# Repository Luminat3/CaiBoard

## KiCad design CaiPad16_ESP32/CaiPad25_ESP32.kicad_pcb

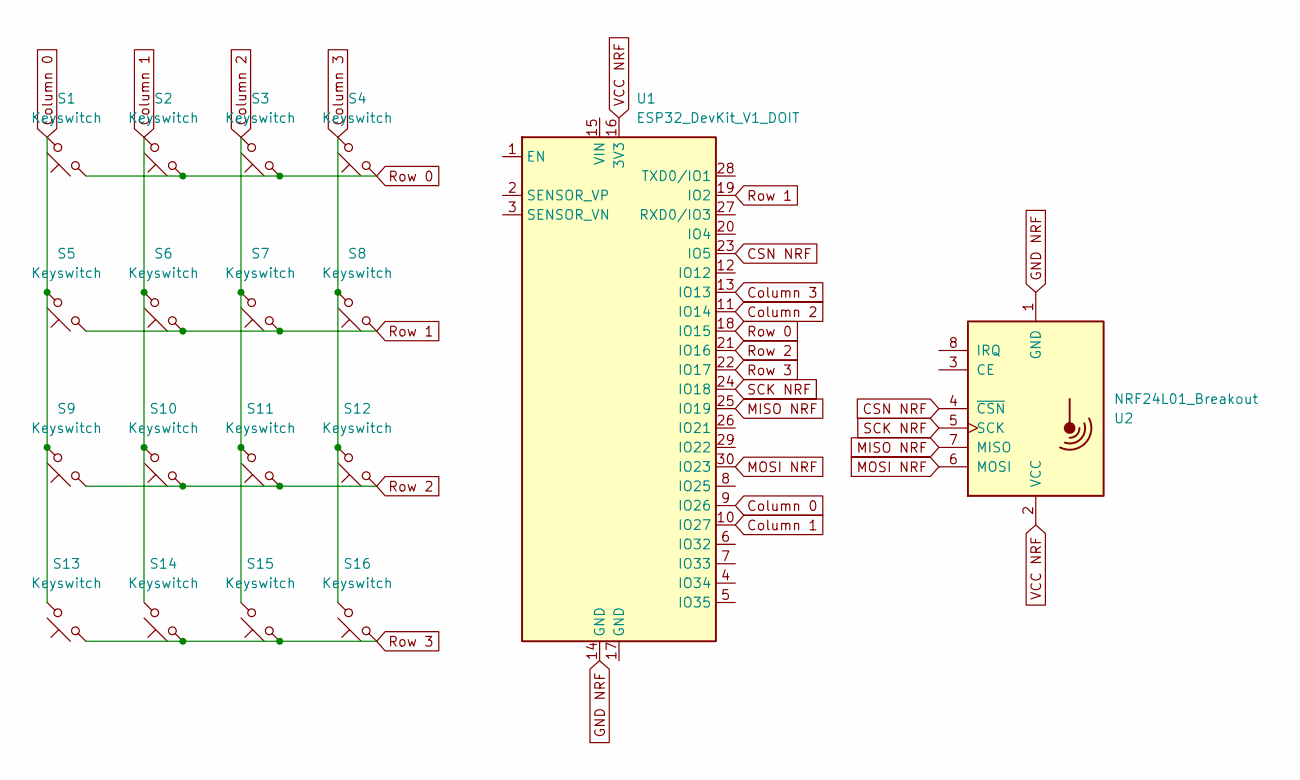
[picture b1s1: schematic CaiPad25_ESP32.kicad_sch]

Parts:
S1, S2, S3, S4, S5, S6, S7, S8, S9, S10, S11, S12, S13, S14, S15, S16: Keyswitch; SW_Cherry_MX_1.00u_PCB
U1: ESP32_DevKit_V1_DOIT; esp32_devkit_v1_doit
U2: NRF24L01_Breakout; nRF24L01_Breakout

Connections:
CSN NRF: U1.23 (IO5), U2.4 (~CSN)
Column 0: S1.2, S5.2, S9.2, S13.2, U1.9 (IO26)
Column 1: S2.2, S6.2, S10.2, S14.2, U1.10 (IO27)
Column 2: S3.2, S7.2, S11.2, S15.2, U1.11 (IO14)
Column 3: S4.2, S8.2, S12.2, S16.2, U1.13 (IO13)
GND NRF: U1.14 (GND), U2.1 (GND)
MISO NRF: U1.25 (IO19), U2.7 (MISO)
MOSI NRF: U1.30 (IO23), U2.6 (MOSI)
Row 0: S1.1, S2.1, S3.1, S4.1, U1.18 (IO15)
Row 1: S5.1, S6.1, S7.1, S8.1, U1.19 (IO2)
Row 2: S9.1, S10.1, S11.1, S12.1, U1.21 (IO16)
Row 3: S13.1, S14.1, S15.1, S16.1, U1.22 (IO17)
SCK NRF: U1.24 (IO18), U2.5 (SCK)
VCC NRF: U1.16 (3V3), U2.2 (VCC)

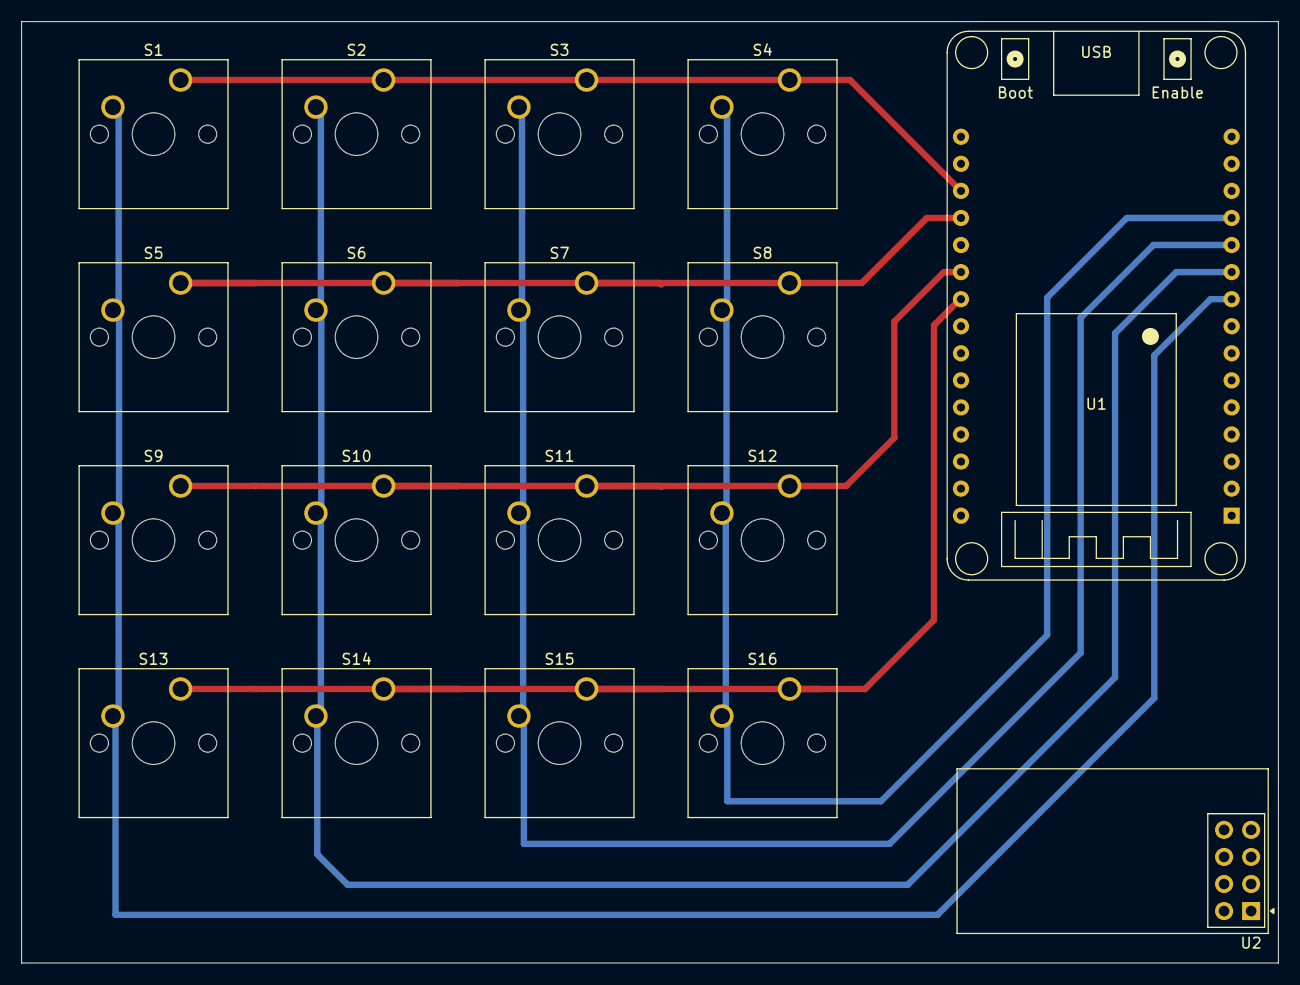
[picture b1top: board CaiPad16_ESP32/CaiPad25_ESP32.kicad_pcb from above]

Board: 2 copper layers, 117.9 x 88.3 mm, 18 parts (0 on the bottom side), 14 nets.

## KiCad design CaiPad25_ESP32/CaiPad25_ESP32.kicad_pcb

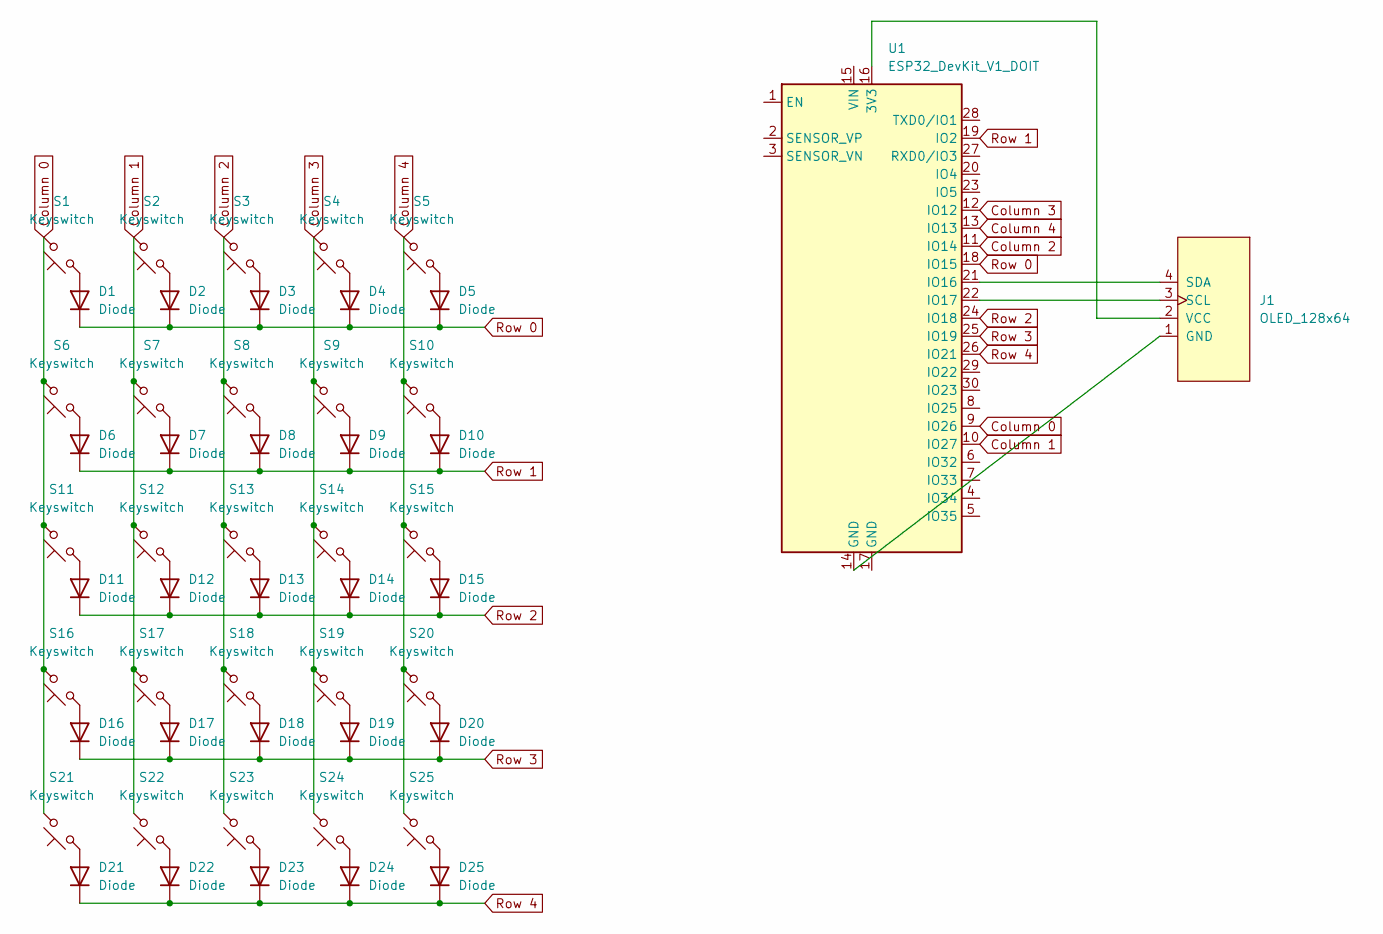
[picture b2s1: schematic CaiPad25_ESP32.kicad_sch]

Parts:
D1, D2, D3, D4, D5, D6, D7, D8, D9, D10, D11, D12, D13, D14, D15, D16, D17, D18, D19, D20, D21, D22, D23, D24, D25: Diode; Diode_DO-35
J1: OLED_128x64
S1, S2, S3, S4, S5, S6, S7, S8, S9, S10, S11, S12, S13, S14, S15, S16, S17, S18, S19, S20, S21, S22, S23, S24, S25: Keyswitch; SW_Cherry_MX_1.00u_PCB
U1: ESP32_DevKit_V1_DOIT; esp32_devkit_v1_doit

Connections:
Column 0: S1.2, S6.2, S11.2, S16.2, S21.2, U1.9 (IO26)
Column 1: S2.2, S7.2, S12.2, S17.2, S22.2, U1.10 (IO27)
Column 2: S3.2, S8.2, S13.2, S18.2, S23.2, U1.11 (IO14)
Column 3: S4.2, S9.2, S14.2, S19.2, S24.2, U1.12 (IO12)
Column 4: S5.2, S10.2, S15.2, S20.2, S25.2, U1.13 (IO13)
unnamed: D1.2 (A), S1.1
unnamed: D2.2 (A), S2.1
unnamed: D3.2 (A), S3.1
unnamed: D4.2 (A), S4.1
unnamed: D5.2 (A), S5.1
unnamed: D6.2 (A), S6.1
unnamed: D7.2 (A), S7.1
unnamed: D8.2 (A), S8.1
unnamed: D9.2 (A), S9.1
unnamed: D10.2 (A), S10.1
unnamed: D11.2 (A), S11.1
unnamed: D12.2 (A), S12.1
unnamed: D13.2 (A), S13.1
unnamed: D14.2 (A), S14.1
unnamed: D15.2 (A), S15.1
unnamed: D16.2 (A), S16.1
unnamed: D17.2 (A), S17.1
unnamed: D18.2 (A), S18.1
unnamed: D19.2 (A), S19.1
unnamed: D20.2 (A), S20.1
unnamed: D21.2 (A), S21.1
unnamed: D22.2 (A), S22.1
unnamed: D23.2 (A), S23.1
unnamed: D24.2 (A), S24.1
unnamed: D25.2 (A), S25.1
unnamed: J1.1 (GND), U1.14 (GND)
unnamed: J1.3 (SCL), U1.22 (IO17)
unnamed: J1.4 (SDA), U1.21 (IO16)
unnamed: J1.2 (VCC), U1.16 (3V3)
Row 0: D1.1 (K), D2.1 (K), D3.1 (K), D4.1 (K), D5.1 (K), U1.18 (IO15)
Row 1: D6.1 (K), D7.1 (K), D8.1 (K), D9.1 (K), D10.1 (K), U1.19 (IO2)
Row 2: D11.1 (K), D12.1 (K), D13.1 (K), D14.1 (K), D15.1 (K), U1.24 (IO18)
Row 3: D16.1 (K), D17.1 (K), D18.1 (K), D19.1 (K), D20.1 (K), U1.25 (IO19)
Row 4: D21.1 (K), D22.1 (K), D23.1 (K), D24.1 (K), D25.1 (K), U1.26 (IO21)

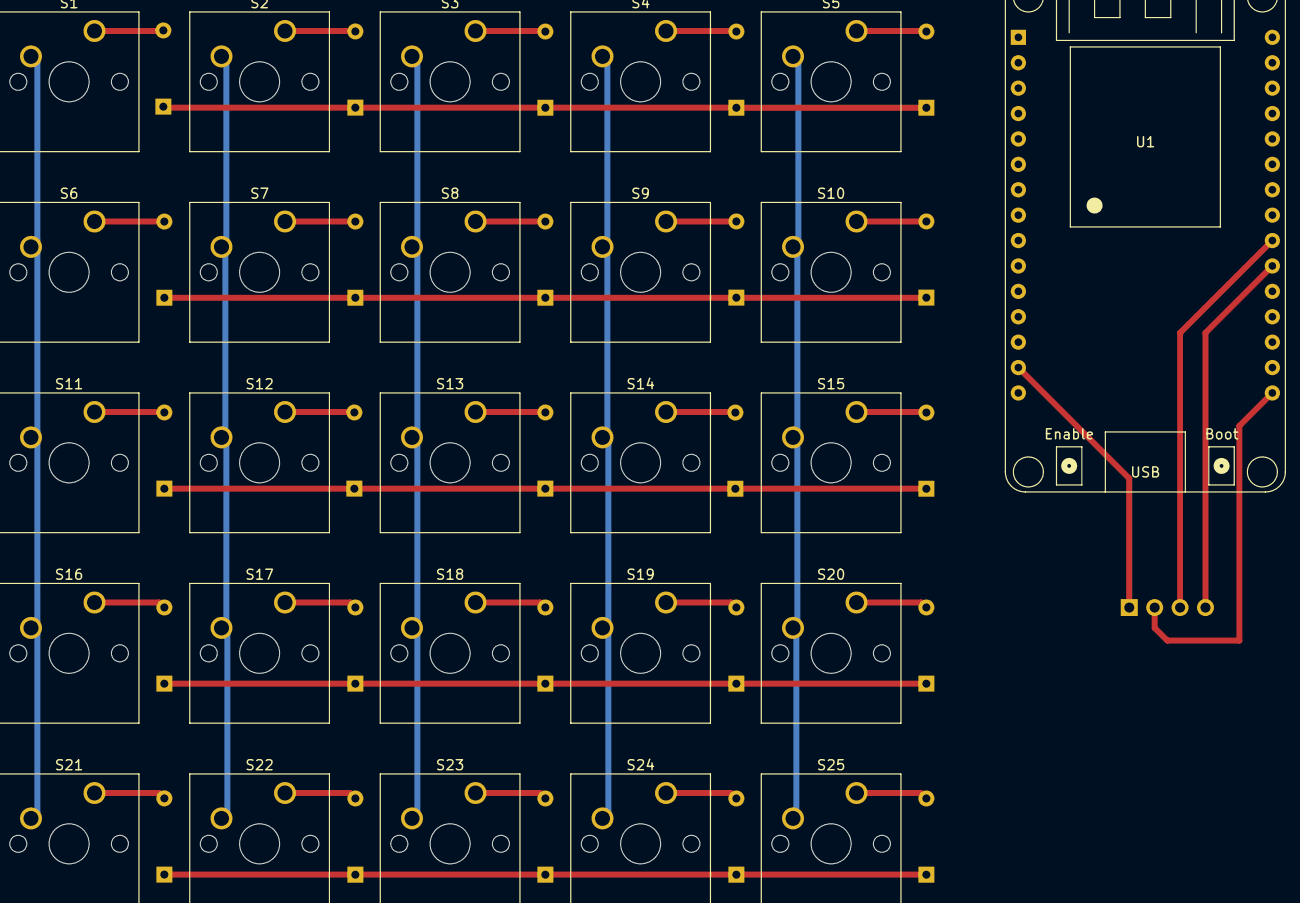
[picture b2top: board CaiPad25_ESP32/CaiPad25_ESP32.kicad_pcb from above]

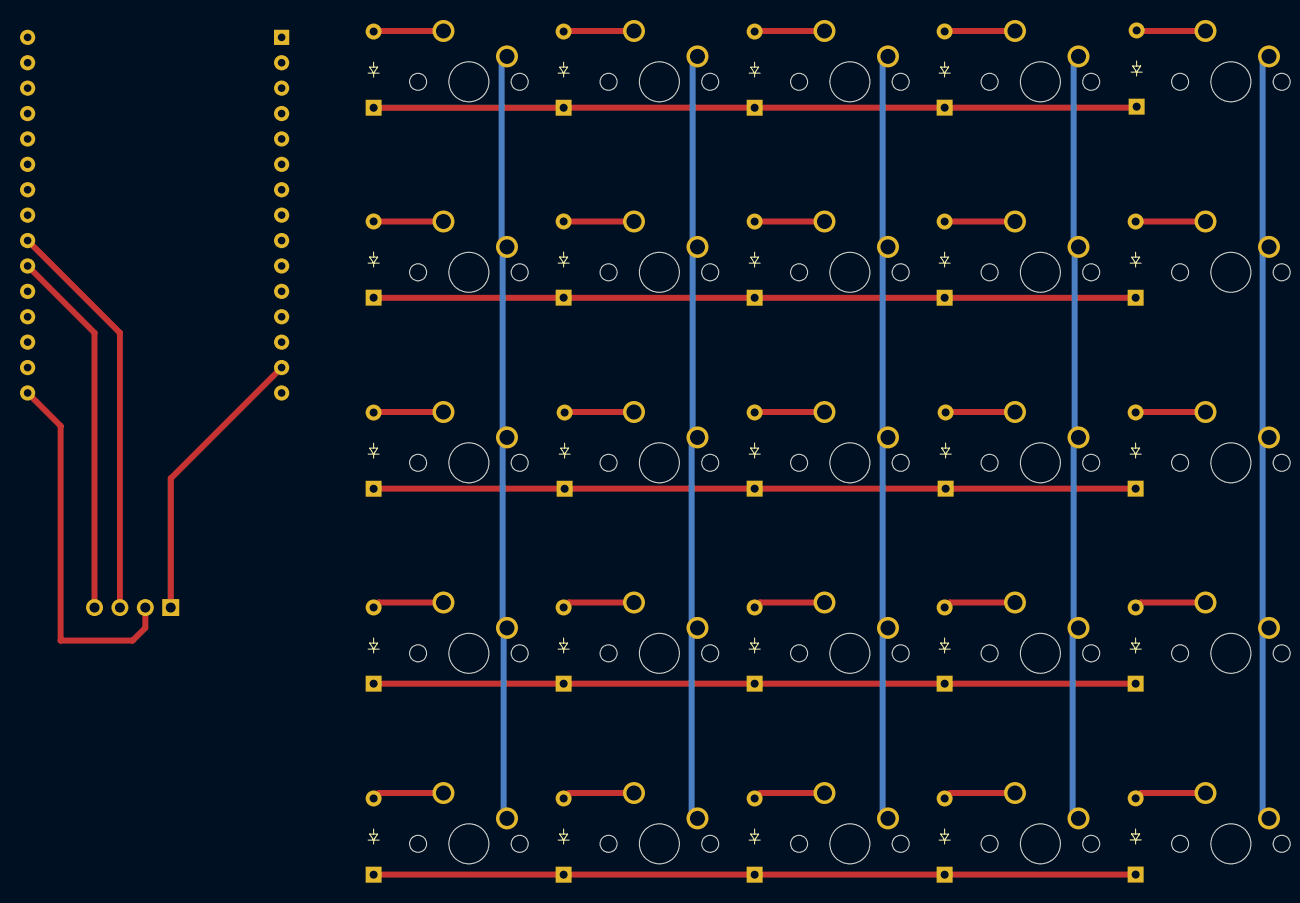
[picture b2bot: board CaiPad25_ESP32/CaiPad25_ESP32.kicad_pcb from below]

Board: 2 copper layers, 52 parts (25 on the bottom side), 39 nets.

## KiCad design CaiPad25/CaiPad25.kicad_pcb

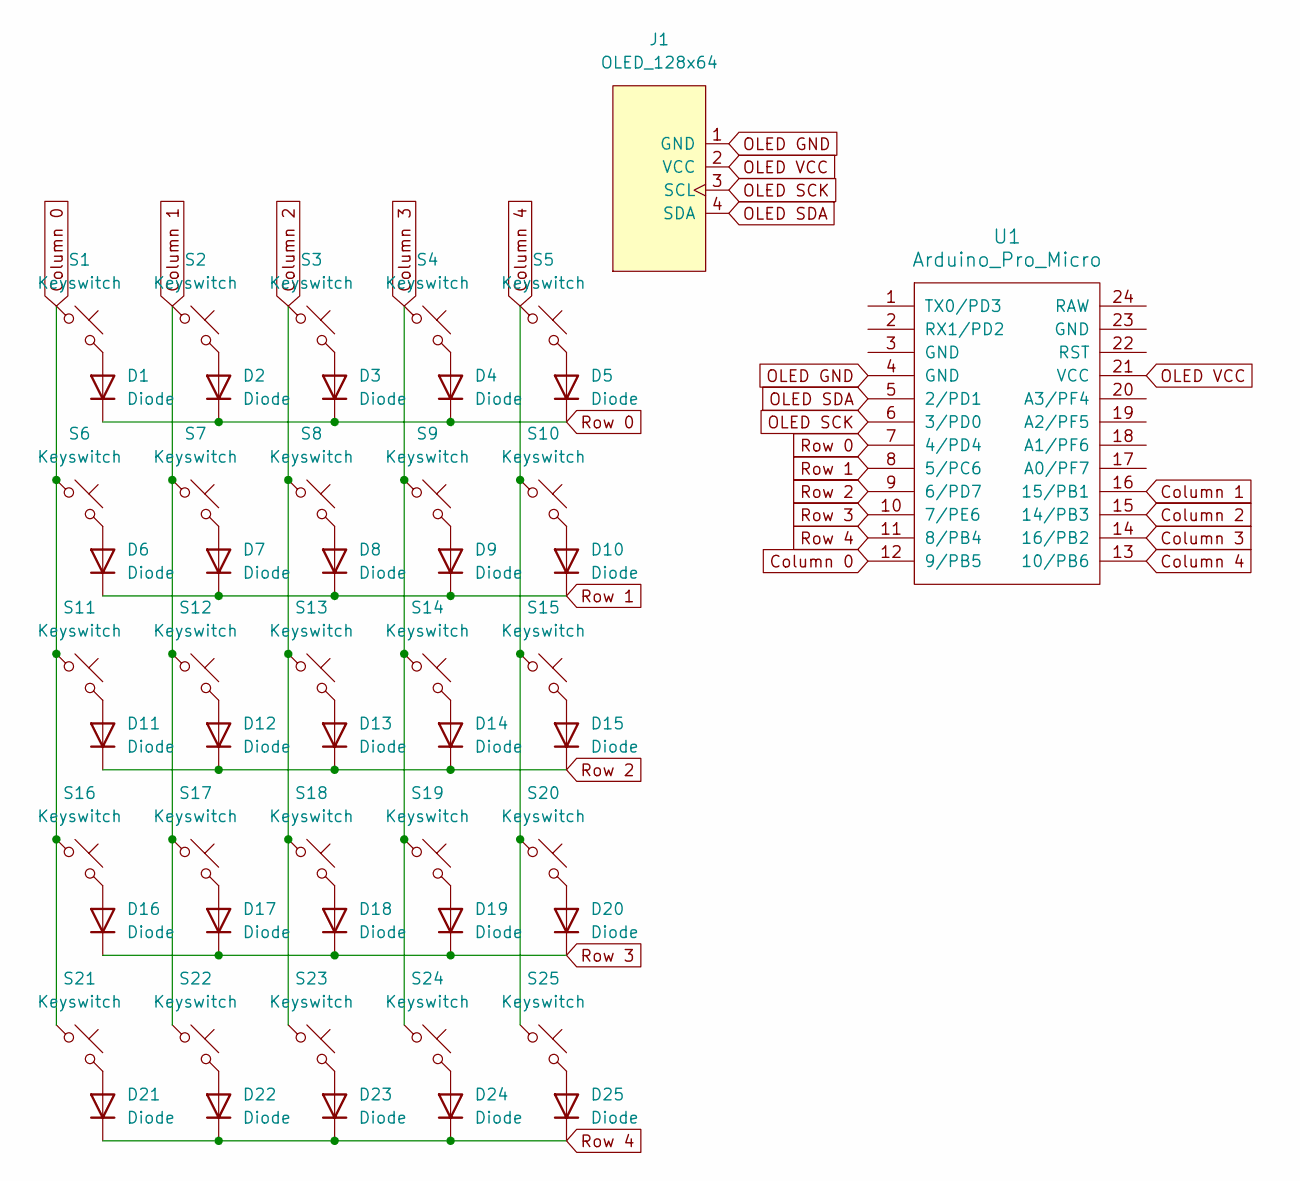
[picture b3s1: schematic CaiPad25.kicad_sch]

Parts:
D1, D2, D3, D4, D5, D6, D7, D8, D9, D10, D11, D12, D13, D14, D15, D16, D17, D18, D19, D20, D21, D22, D23, D24, D25: Diode; Diode_DO-35
J1: OLED_128x64
S1, S2, S3, S4, S5, S6, S7, S8, S9, S10, S11, S12, S13, S14, S15, S16, S17, S18, S19, S20, S21, S22, S23, S24, S25: Keyswitch; MX_PCB_1.00u
U1: Arduino_Pro_Micro

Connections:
Column 0: S1.1, S6.1, S11.1, S16.1, S21.1, U1.12 (9/PB5)
Column 1: S2.1, S7.1, S12.1, S17.1, S22.1, U1.16 (15/PB1)
Column 2: S3.1, S8.1, S13.1, S18.1, S23.1, U1.15 (14/PB3)
Column 3: S4.1, S9.1, S14.1, S19.1, S24.1, U1.14 (16/PB2)
Column 4: S5.1, S10.1, S15.1, S20.1, S25.1, U1.13 (10/PB6)
unnamed: D1.2 (A), S1.2
unnamed: D2.2 (A), S2.2
unnamed: D3.2 (A), S3.2
unnamed: D4.2 (A), S4.2
unnamed: D5.2 (A), S5.2
unnamed: D6.2 (A), S6.2
unnamed: D7.2 (A), S7.2
unnamed: D8.2 (A), S8.2
unnamed: D9.2 (A), S9.2
unnamed: D10.2 (A), S10.2
unnamed: D11.2 (A), S11.2
unnamed: D12.2 (A), S12.2
unnamed: D13.2 (A), S13.2
unnamed: D14.2 (A), S14.2
unnamed: D15.2 (A), S15.2
unnamed: D16.2 (A), S16.2
unnamed: D17.2 (A), S17.2
unnamed: D18.2 (A), S18.2
unnamed: D19.2 (A), S19.2
unnamed: D20.2 (A), S20.2
unnamed: D21.2 (A), S21.2
unnamed: D22.2 (A), S22.2
unnamed: D23.2 (A), S23.2
unnamed: D24.2 (A), S24.2
unnamed: D25.2 (A), S25.2
OLED GND: J1.1 (GND), U1.4 (GND)
OLED SCK: J1.3 (SCL), U1.6 (3/PD0)
OLED SDA: J1.4 (SDA), U1.5 (2/PD1)
OLED VCC: J1.2 (VCC), U1.21 (VCC)
Row 0: D1.1 (K), D2.1 (K), D3.1 (K), D4.1 (K), D5.1 (K), U1.7 (4/PD4)
Row 1: D6.1 (K), D7.1 (K), D8.1 (K), D9.1 (K), D10.1 (K), U1.8 (5/PC6)
Row 2: D11.1 (K), D12.1 (K), D13.1 (K), D14.1 (K), D15.1 (K), U1.9 (6/PD7)
Row 3: D16.1 (K), D17.1 (K), D18.1 (K), D19.1 (K), D20.1 (K), U1.10 (7/PE6)
Row 4: D21.1 (K), D22.1 (K), D23.1 (K), D24.1 (K), D25.1 (K), U1.11 (8/PB4)

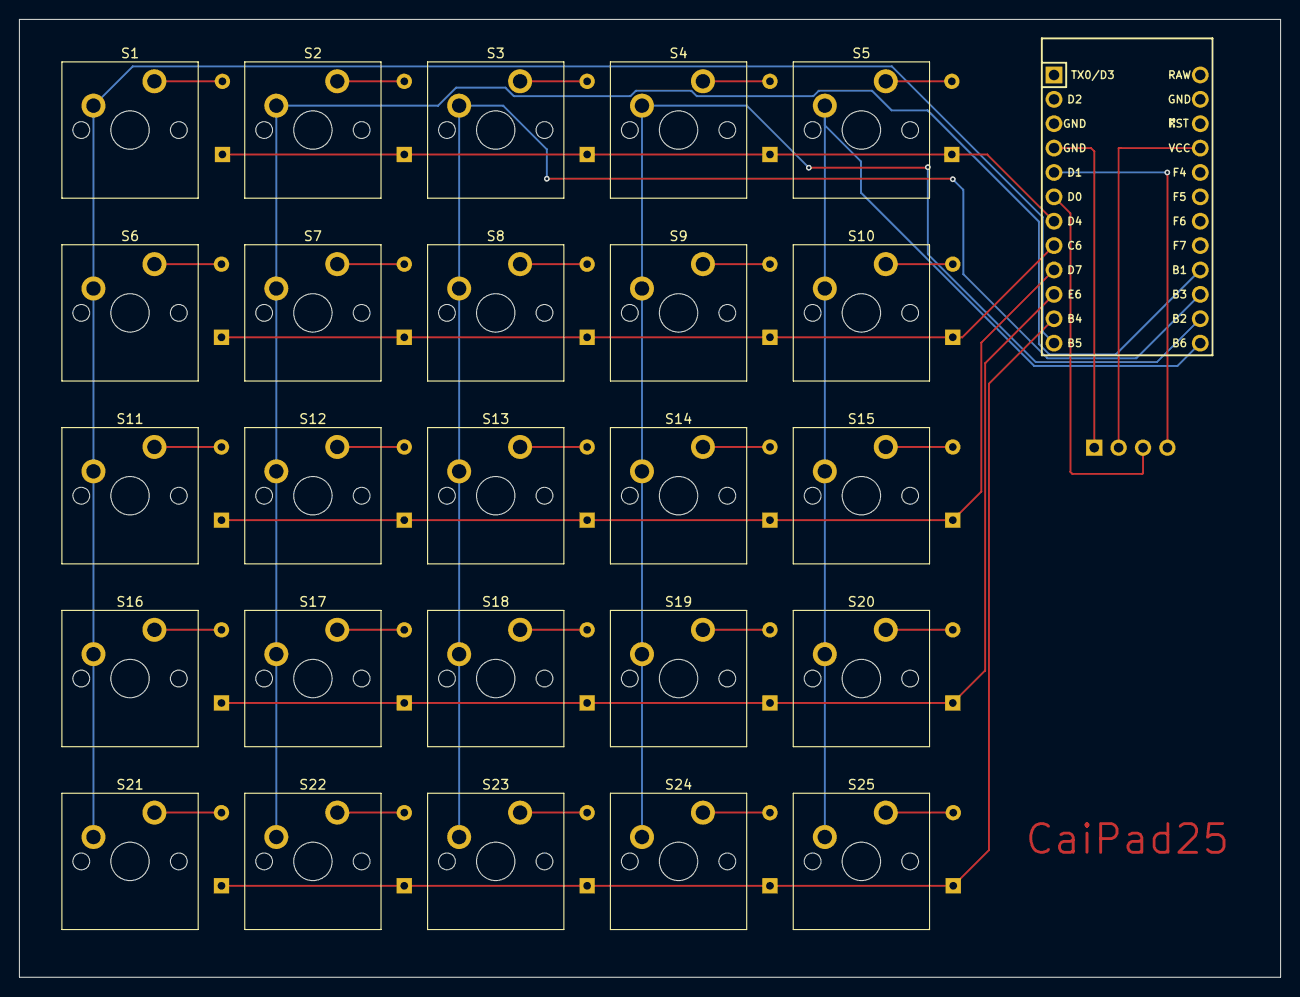
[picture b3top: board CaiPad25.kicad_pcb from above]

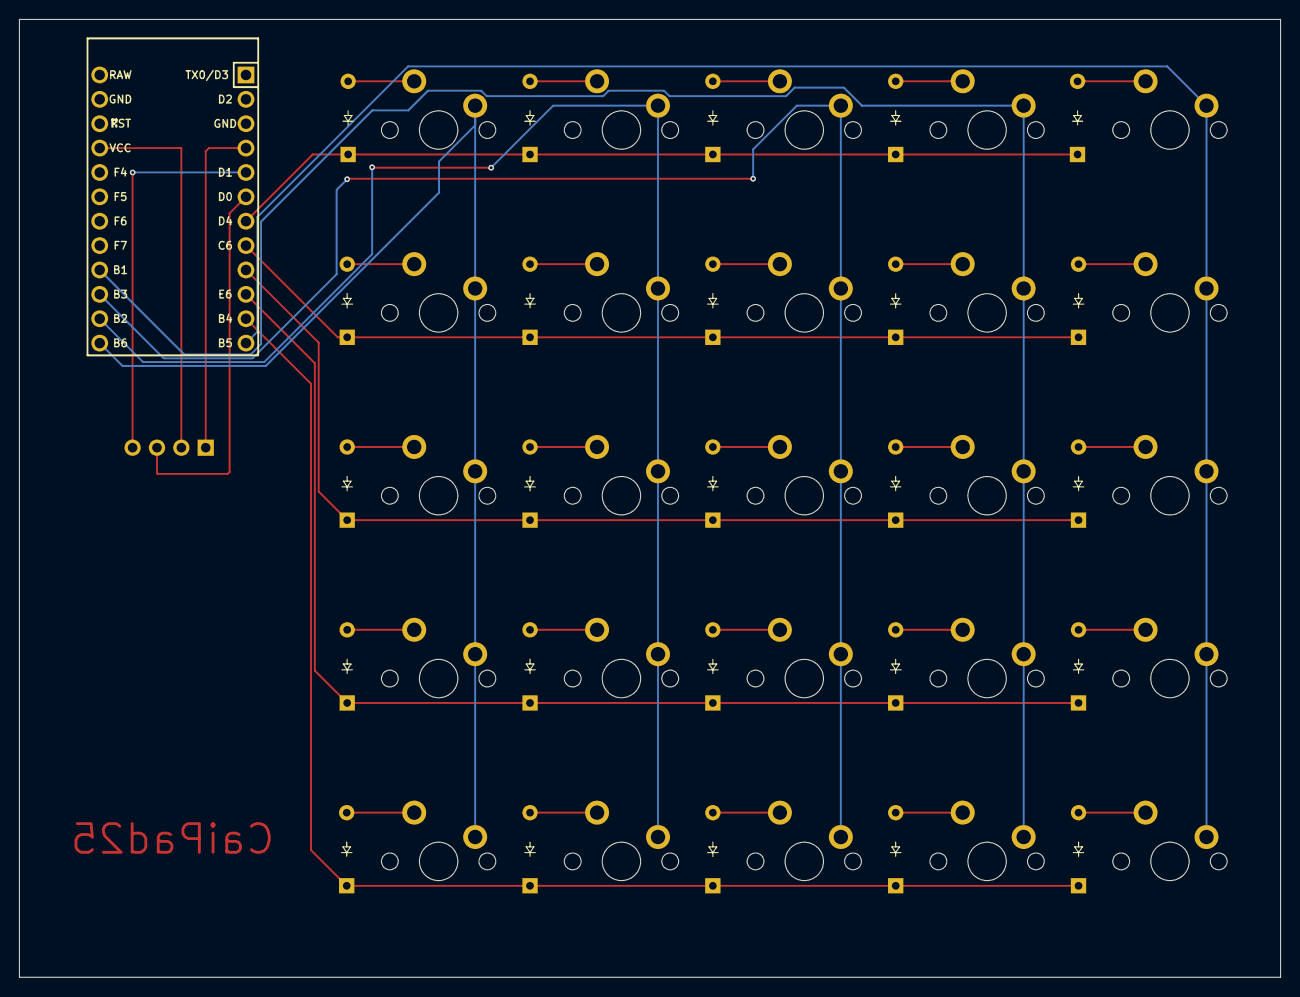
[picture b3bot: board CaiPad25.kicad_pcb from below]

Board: 2 copper layers, 131.4 x 99.8 mm, 52 parts (25 on the bottom side), 39 nets.

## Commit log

2024-10-21 first upload
2024-11-15 update on CaiPad25_ESP32
2024-11-15 adding firmware for the esp32 version of the board
2024-11-22 major changes
2024-11-28 Update on the AcaiPad25 to AcaiPad16
2024-12-06 added pro micro firmware
2024-12-10 FEAT ~ add wifi and post request every 10 seconds
